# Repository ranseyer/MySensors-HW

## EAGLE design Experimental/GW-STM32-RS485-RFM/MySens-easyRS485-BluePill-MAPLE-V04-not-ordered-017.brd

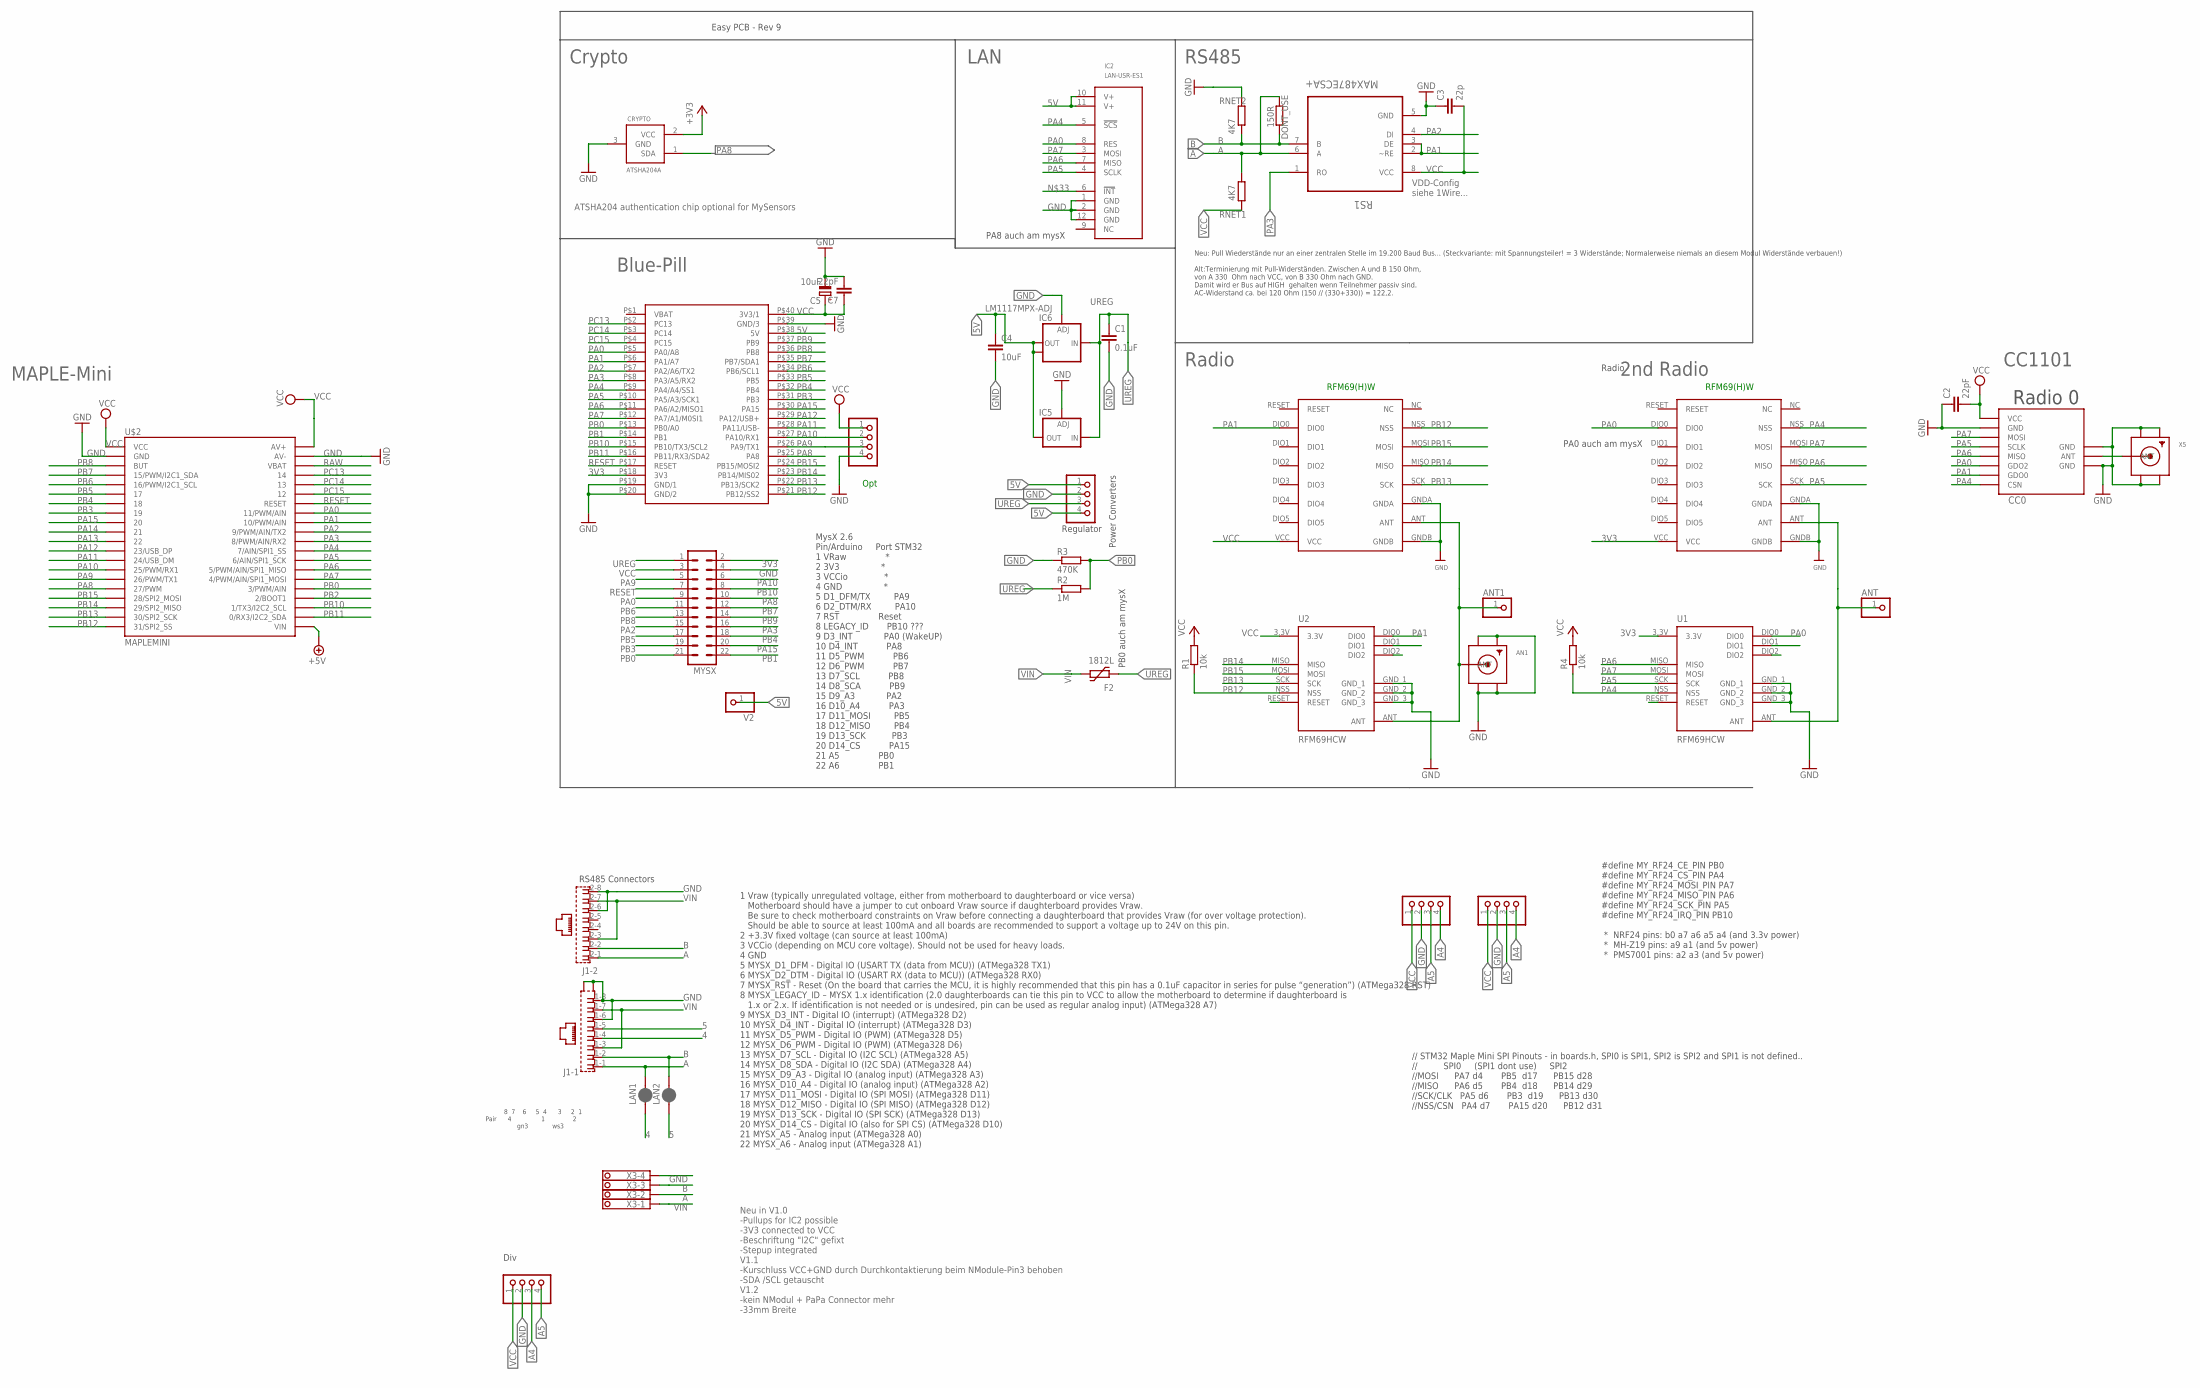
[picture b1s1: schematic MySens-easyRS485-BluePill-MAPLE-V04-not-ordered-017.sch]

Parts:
AN1: SMACONNECTOR_EDGE; SMA_EDGELAUNCH
ANT, ANT1: PINHD-1X1; 1X01
BH1750: PINHD-1X04_2.54-S; 1X04-S
C1: 0.1uF; C1206
C2, C7: 22pF; C0805
C3: 22p; C0805
C4: 10uF; C1210
C5: 10uF; R/2012-12W
CC0: CC1101; CC1101_MODULE1_SMD
CRYPTO: ATSHA204A; SOT23
DBG: PINHD-1X04_2.54-S; 1X04-S
DONT_USE: 150R; R0805
F2: 1812L
I2C-1, I2C-2: PINHD-1X04_2.54-S; 1X04-S
IC2: LAN-USR-ES1; USR-ES1
IC5: LD117ADT50TR; DPACK
IC6: LM1117MPX-ADJ; SOT223
J1: RJ45_2X_NARROW_SHILDPINS_NOCASE
LAN1, LAN2: JUMPER-SMT_2_NC_PASTE_SILK; SMT-JUMPER_2_NC_PASTE_SILK
MYSX: MA11-2
R1, R4: 10k; M0805
R2: 1M; R0805
R3: 470K; R0805
RFM69W, RFM69W1: RFM69HW; RFM
RNET1, RNET2: 4K7; R0805
RS1: MAX487ECSA+; SOIC127P600X175-8N
STEPDWN: PINHD-1X04_2.54-S; 1X04-S
U1, U2: RFM69HCW; RFM69HCW-XXXS2
U$2: MAPLEMINI; 20-DIP
U$4: BLUEPILL
V2: PINHD-1X1; 1X01
X3: 1751264
X5: SMACONNECTOR_EDGE; SMA_EDGELAUNCH

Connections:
3V3: CRYPTO.2 (VCC), MYSX.2, RFM69W.VCC, U1.3.3V, U$4.P$18 (3V3)
4: J1.1-4 (4), LAN1.1
5: J1.1-5 (5), LAN2.1
5V: C4.1, IC2.10 (V+), IC2.11 (V+), IC5.4 (OUT), IC6.2 (OUT), IC6.TAB (OUT1), STEPDWN.1, STEPDWN.4, U$4.P$38 (5V), V2.1
+5V: U$2.21 (VIN)
A: DONT_USE.1, J1.1-1 (1), J1.2-1 (1), LAN1.2, RNET1.2, RS1.6 (A), X3.2
A4: BH1750.4, I2C-1.4, I2C-2.3
A5: BH1750.3, I2C-1.3, I2C-2.4
ANT0: CC0.ANT, X5.P (ANT)
ANT1: AN1.P (ANT), ANT1.1, RFM69W1.ANT, U2.ANT
ANT2: ANT.1, RFM69W.ANT, U1.ANT
B: DONT_USE.2, J1.1-2 (2), J1.2-2 (2), LAN2.2, RNET2.1, RS1.7 (B), X3.3
GND: AN1.GND@1 (GND4), AN1.GND@2 (GND3), AN1.GND@3 (GND2), AN1.GND@4 (GND1), BH1750.2, C1.2, C2.1, C3.1, C4.2, C5.-, C7.2, CC0.GND@0 (GND), CC0.GND@1 (GND), CC0.GND@2 (GND), CRYPTO.3 (GND), DBG.4, I2C-1.2, I2C-2.2, IC2.1 (GND), IC2.2 (GND), IC2.12 (GND), IC5.1 (ADJ), IC6.1 (ADJ), J1.1-6 (6), J1.1-8 (8), J1.2-6 (6), J1.2-8 (8), J1.G1 (S1), J1.G3 (S2), MYSX.4, R3.1, RFM69W.GNDA, RFM69W.GNDB, RFM69W1.GNDA, RFM69W1.GNDB, RNET2.2, RS1.5 (GND), STEPDWN.2, U1.GND_1, U1.GND_2, U1.GND_3, U2.GND_1, U2.GND_2, U2.GND_3, U$2.2 (GND), U$2.39 (AV-), U$4.P$19 (GND/1), U$4.P$20 (GND/2), U$4.P$39 (GND/3), X3.4, X5.GND@1 (GND4), X5.GND@2 (GND3), X5.GND@3 (GND2), X5.GND@4 (GND1)
PA0: CC0.GDO2, IC2.8 (RES), MYSX.9, RFM69W.DIO0, U1.DIO0, U$2.33 (11/PWM/AIN), U$4.P$5 (PA0/A8)
PA1: CC0.GDO0, RFM69W1.DIO0, RS1.2 (~RE), RS1.3 (DE), U2.DIO0, U$2.32 (10/PWM/AIN), U$4.P$6 (PA1/A7)
PA2: MYSX.15, RS1.4 (DI), U$2.31 (9/PWM/AIN/TX2), U$4.P$7 (PA2/A6/TX2)
PA3: MYSX.16, RS1.1 (RO), U$2.30 (8/PWM/AIN/RX2), U$4.P$8 (PA3/A5/RX2)
PA4: CC0.CSN, IC2.5 (!SCS!), R4.1, RFM69W.NSS, U1.NSS, U$2.29 (7/AIN/SPI1_SS), U$4.P$9 (PA4/A4/SS1)
PA5: CC0.SCLK, IC2.4 (SCLK), RFM69W.SCK, U1.SCK, U$2.28 (6/AIN/SPI1_SCK), U$4.P$10 (PA5/A3/SCK1)
PA6: CC0.MISO, IC2.7 (MISO), RFM69W.MISO, U1.MISO, U$2.27 (5/PWM/AIN/SPI1_MISO), U$4.P$11 (PA6/A2/MISO1)
PA7: CC0.MOSI, IC2.3 (MOSI), RFM69W.MOSI, U1.MOSI, U$2.26 (4/PWM/AIN/SPI1_MOSI), U$4.P$12 (PA7/A1/M0SI1)
PA8: CRYPTO.1 (SDA), MYSX.10, U$2.16 (27/PWM), U$4.P$25 (PA8)
PA9: DBG.3, MYSX.5, U$2.15 (26/PWM/TX1), U$4.P$26 (PA9/TX1)
PA10: DBG.2, MYSX.6, U$2.14 (25/PWM/RX1), U$4.P$27 (PA10/RX1)
PA11: U$2.13 (24/USB_DM), U$4.P$28 (PA11/USB-)
PA12: U$2.12 (23/USB_DP), U$4.P$29 (PA12/USB+)
PA13: U$2.11 (22)
PA14: U$2.10 (21)
PA15: MYSX.20, U$2.9 (20), U$4.P$30 (PA15)
PB0: MYSX.21, R2.2, R3.2, U$2.25 (3/PWM/AIN), U$4.P$13 (PB0/A0)
PB1: MYSX.22, U$4.P$14 (PB1)
PB2: U$2.24 (2/BOOT1)
PB3: MYSX.19, U$2.8 (19), U$4.P$31 (PB3)
PB4: MYSX.18, U$2.7 (18), U$4.P$32 (PB4)
PB5: MYSX.17, U$2.6 (17), U$4.P$33 (PB5)
PB6: MYSX.11, U$2.5 (16/PWM/I2C1_SCL), U$4.P$34 (PB6/SCL1)
PB7: MYSX.12, U$2.4 (15/PWM/I2C1_SDA), U$4.P$35 (PB7/SDA1)
PB8: MYSX.13, U$2.3 (BUT), U$4.P$36 (PB8)
PB9: MYSX.14, U$4.P$37 (PB9)
PB10: MYSX.8, U$2.23 (1/TX3/I2C2_SCL), U$4.P$15 (PB10/TX3/SCL2)
PB11: U$2.22 (0/RX3/I2C2_SDA), U$4.P$16 (PB11/RX3/SDA2)
PB12: R1.1, RFM69W1.NSS, U2.NSS, U$2.20 (31/SPI2_SS), U$4.P$21 (PB12/SS2)
PB13: RFM69W1.SCK, U2.SCK, U$2.19 (30/SPI2_SCK), U$4.P$22 (PB13/SCK2)
PB14: RFM69W1.MISO, U2.MISO, U$2.18 (29/SPI2_MISO), U$4.P$23 (PB14/MIS02)
PB15: RFM69W1.MOSI, U2.MOSI, U$2.17 (28/SPI2_MOSI), U$4.P$24 (PB15/MOSI2)
PC13: U$2.37 (14), U$4.P$2 (PC13)
PC14: U$2.36 (13), U$4.P$3 (PC14)
PC15: U$2.35 (12), U$4.P$4 (PC15)
RAW: U$2.38 (VBAT)
RESET: MYSX.7, U$2.34 (RESET), U$4.P$17 (RESET)
UREG: C1.1, F2.P$1 (1), IC5.3 (IN), IC6.3 (IN), MYSX.1, R2.1, STEPDWN.3
VCC: BH1750.1, C2.2, C3.2, C5.+, C7.1, CC0.VCC, DBG.1, I2C-1.1, I2C-2.1, MYSX.3, R1.2, R4.2, RFM69W1.VCC, RNET1.1, RS1.8 (VCC), U2.3.3V, U$2.1 (VCC), U$2.40 (AV+), U$4.P$40 (3V3/1)
VIN: F2.P$2 (2), J1.1-3 (3), J1.1-7 (7), J1.2-3 (3), J1.2-7 (7), X3.1

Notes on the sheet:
Easy PCB - Rev 9
ATSHA204 authentication chip optional for MySensors
RFM69(H)W
Radio
VDD-Config siehe 1Wire...
Neu: Pull Wiederstände nur an einer zentralen Stelle im 19.200 Baud Bus... (Steckvariante: mit Spannungsteiler! = 3 Widerstände; Normalerweise niemals an diesem Modul Widerstände verbauen!) Alt:Terminierung mit Pull-Widerständen. Zwischen A und B 150 Ohm, von A 330 Ohm nach VCC, von B 330 Ohm nach 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
Opt
Blue-Pill
// STM32 Maple Mini SPI Pinouts - in boards.h, SPI0 is SPI1, SPI2 is SPI2 and SPI1 is not defined.. // SPI0 (SPI1 dont use) SPI2 //MOSI PA7 d4 PB5 d17 PB15 d28 //MISO PA6 d5 PB4 d18 PB14 d29 //SCK/CLK PA5 d6 PB3 d19 PB13 d30 //NSS/CSN PA4 d7 PA15 d20 PB12 d31
#define MY_RF24_CE_PIN PB0 #define MY_RF24_CS_PIN PA4 #define MY_RF24_MOSI_PIN PA7 #define MY_RF24_MISO_PIN PA6 #define MY_RF24_SCK_PIN PA5 #define MY_RF24_IRQ_PIN PB10 * NRF24 pins: b0 a7 a6 a5 a4 (and 3.3v power) * MH-Z19 pins: a9 a1 (and 5v power) * PMS7001 pins: a2 a3 (and 5v power)
Power Converters
Regulator
Div
Neu in V1.0 -Pullups for IC2 possible -3V3 connected to VCC -Beschriftung "I2C" gefixt -Stepup integrated V1.1 -Kurschluss VCC+GND durch Durchkontaktierung beim NModule-Pin3 behoben -SDA /SCL getauscht V1.2 -kein NModul + PaPa Connector mehr -33mm Breite
8 7 6 5 4 3 2 1 Pair 4 1 2 gn3 ws3
RS485 Connectors
1 Vraw (typically unregulated voltage, either from motherboard to daughterboard or vice versa) Motherboard should have a jumper to cut onboard Vraw source if daughterboard provides Vraw. Be sure to check motherboard constraints on Vraw before connecting a daughterboard that provides Vraw (for over 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
MysX 2.6 Pin/Arduino Port STM32 1 VRaw * 2 3V3 * 3 VCCio * 4 GND * 5 D1_DFM/TX PA9 6 D2_DTM/RX PA10 7 RST Reset 8 LEGACY_ID PB10 ??? 9 D3_INT PA0 (WakeUP) 10 D4_INT PA8 11 D5_PWM PB6 12 D6_PWM PB7 13 D7_SCL PB8 14 D8_SCA PB9 15 D9_A3 PA2 16 D10_A4 PA3 17 D11_MOSI PB5 18 D12_MISO PB4 19 D13_SCK PB3 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
PA0 auch am mysX
PB0 auch am mysX
PA8 auch am mysX
2nd Radio
LAN
RS485
Crypto
Radio 0
CC1101
MAPLE-Mini

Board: 2 copper layers, 41 parts (18 on the bottom side), 48 nets, no tracks yet.

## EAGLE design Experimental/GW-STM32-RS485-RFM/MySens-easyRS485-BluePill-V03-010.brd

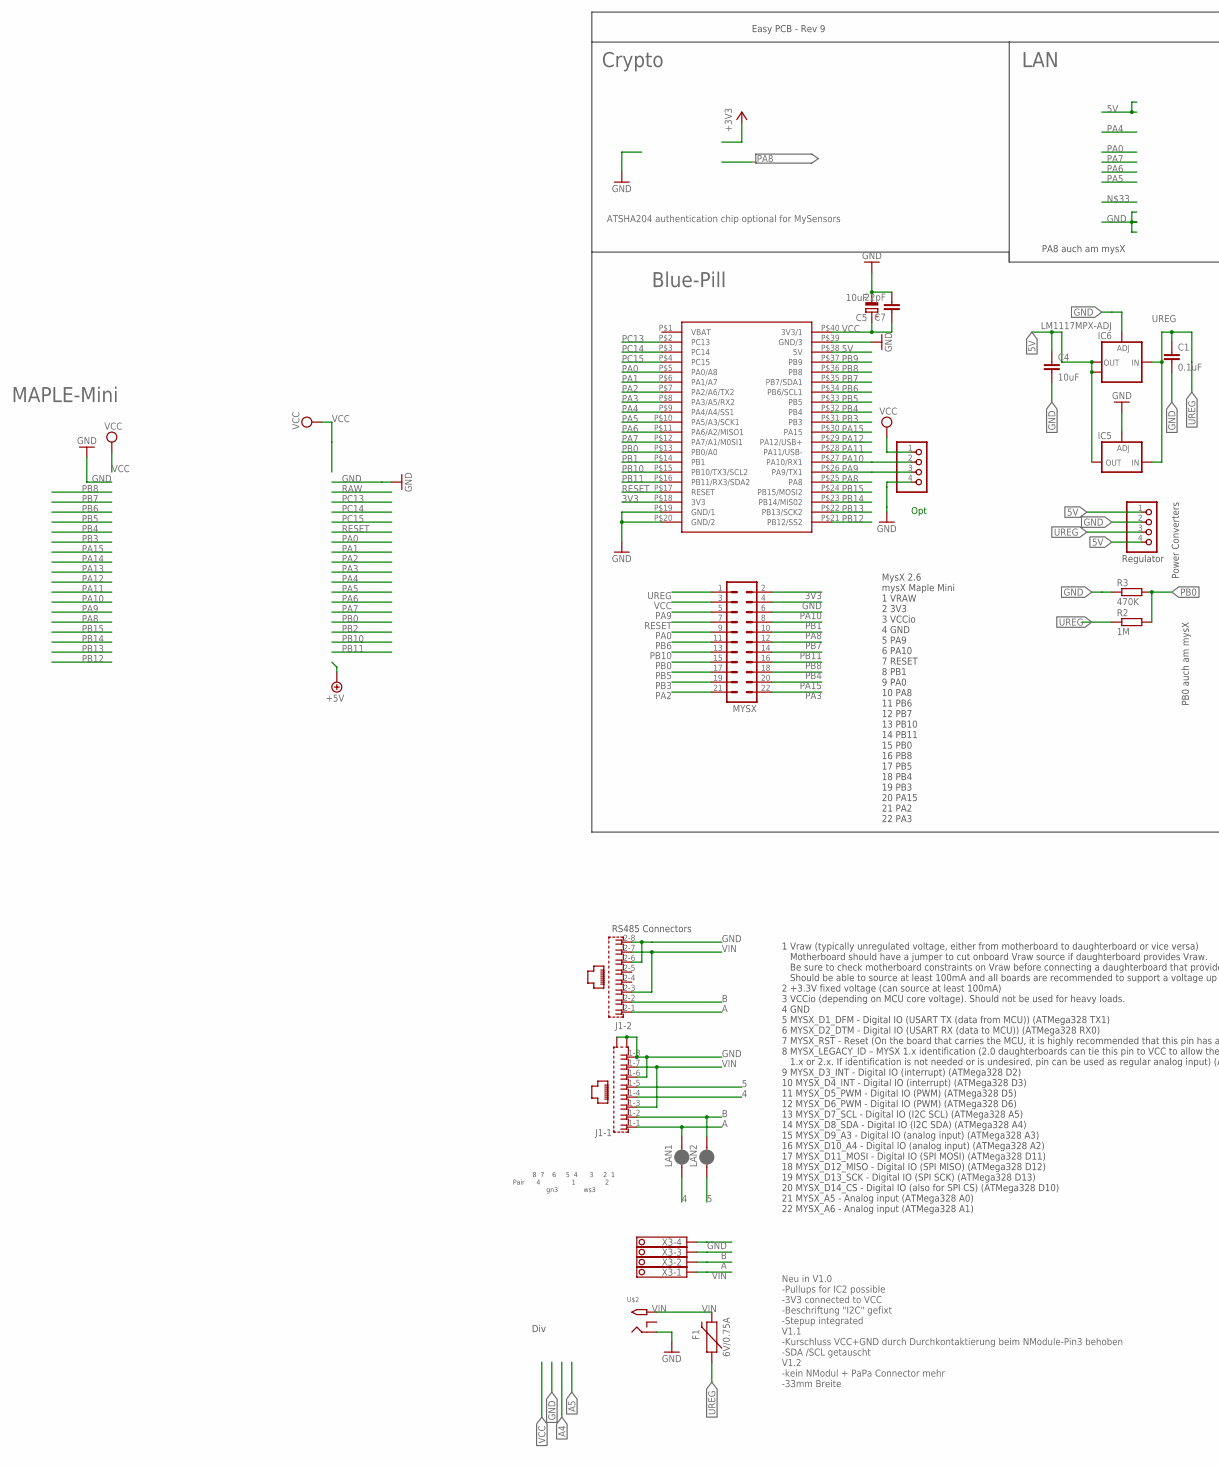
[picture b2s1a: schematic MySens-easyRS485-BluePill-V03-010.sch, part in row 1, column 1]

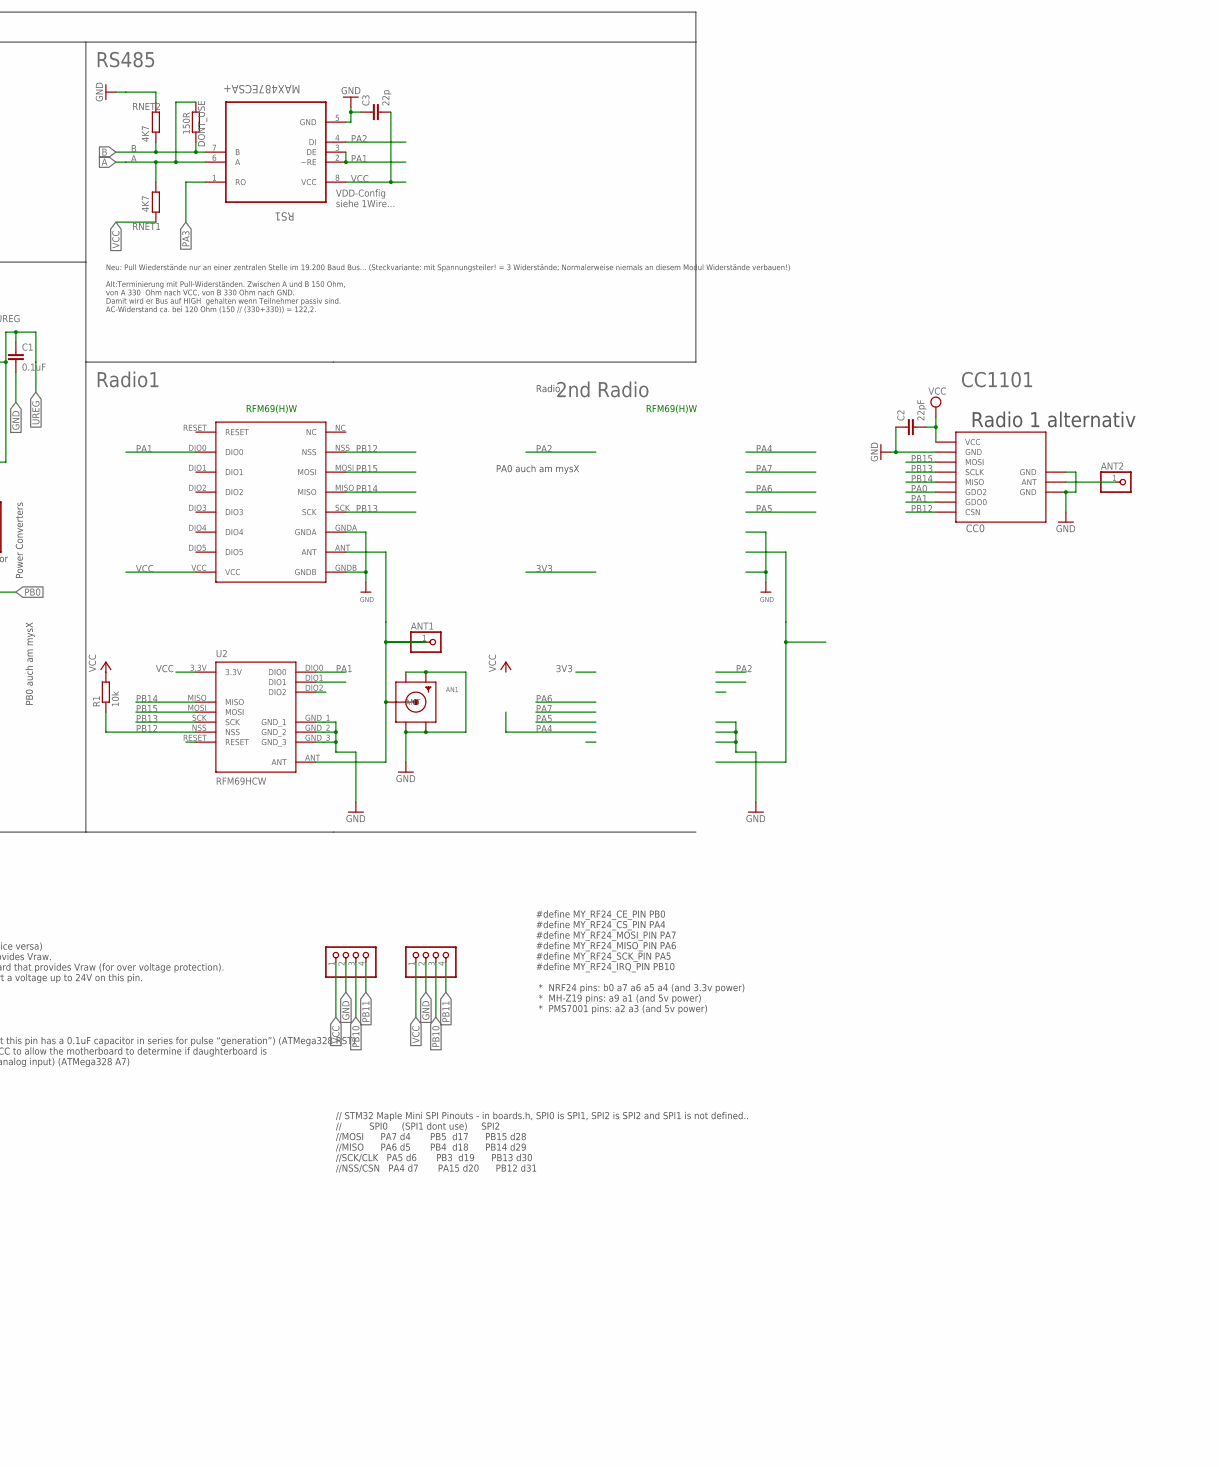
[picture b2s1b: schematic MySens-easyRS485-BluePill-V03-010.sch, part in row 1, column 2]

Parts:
AN1: SMACONNECTOR_EDGE; SMA_EDGELAUNCH
ANT1, ANT2: PINHD-1X1; 1X01
BH1750: PINHD-1X04_2.54-S; 1X04-S
C1: 0.1uF; C1206
C2, C7: 22pF; C0805
C3: 22p; C0805
C4: 10uF; C1210
C5: 10uF; R/2012-12W
CC0: CC1101; CC1101_MODULE1_SMD
DBG: PINHD-1X04_2.54-S; 1X04-S
DONT_USE: 150R; R0805
F1: 6V/0.75A; 1206
I2C-1: PINHD-1X04_2.54-S; 1X04-S
IC5: LD117ADT50TR; DPACK
IC6: LM1117MPX-ADJ; SOT223
J1: RJ45_2X_S
LAN1, LAN2: JUMPER-SMT_2_NC_PASTE_SILK; SMT-JUMPER_2_NC_PASTE_SILK
MYSX: MA11-2
R1: 10k; M0805
R2: 1M; R0805
R3: 470K; R0805
RFM69W1: RFM69HW; RFM
RNET1, RNET2: 4K7; R0805
RS1: MAX487ECSA+; SOIC127P600X175-8N
STEPDWN: PINHD-1X04_2.54-S; 1X04-S
U2: RFM69HCW; RFM69HCW-XXXS2
U$2: 2.1MMJACKTHM; PJ-102A
U$4: BLUEPILL
X3: 1751264

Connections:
3V3: MYSX.2, U$4.P$18 (3V3)
4: J1.1-4 (4), LAN1.1
5: J1.1-5 (5), LAN2.1
5V: C4.1, IC5.4 (OUT), IC6.2 (OUT), IC6.TAB (OUT1), STEPDWN.1, STEPDWN.4, U$4.P$38 (5V)
A: DONT_USE.1, J1.1-1 (1), J1.2-1 (1), LAN1.2, RNET1.2, RS1.6 (A), X3.2
ANT0: ANT2.1, CC0.ANT
ANT1: AN1.P (ANT), ANT1.1, RFM69W1.ANT, U2.ANT
B: DONT_USE.2, J1.1-2 (2), J1.2-2 (2), LAN2.2, RNET2.1, RS1.7 (B), X3.3
GND: AN1.GND@1 (GND4), AN1.GND@2 (GND3), AN1.GND@3 (GND2), AN1.GND@4 (GND1), BH1750.2, C1.2, C2.1, C3.1, C4.2, C5.-, C7.2, CC0.GND@0 (GND), CC0.GND@1 (GND), CC0.GND@2 (GND), DBG.4, I2C-1.2, IC5.1 (ADJ), IC6.1 (ADJ), J1.1-6 (6), J1.1-8 (8), J1.2-6 (6), J1.2-8 (8), J1.G1 (S2), J1.G3 (S1), MYSX.4, R3.1, RFM69W1.GNDA, RFM69W1.GNDB, RNET2.2, RS1.5 (GND), STEPDWN.2, U2.GND_1, U2.GND_2, U2.GND_3, U$2.RING, U$4.P$19 (GND/1), U$4.P$20 (GND/2), U$4.P$39 (GND/3), X3.4
PA0: CC0.GDO2, MYSX.9, U$4.P$5 (PA0/A8)
PA1: CC0.GDO0, RFM69W1.DIO0, RS1.2 (~RE), RS1.3 (DE), U2.DIO0, U$4.P$6 (PA1/A7)
PA2: MYSX.21, RS1.4 (DI), U$4.P$7 (PA2/A6/TX2)
PA3: MYSX.22, RS1.1 (RO), U$4.P$8 (PA3/A5/RX2)
PA4: U$4.P$9 (PA4/A4/SS1)
PA5: U$4.P$10 (PA5/A3/SCK1)
PA6: U$4.P$11 (PA6/A2/MISO1)
PA7: U$4.P$12 (PA7/A1/M0SI1)
PA8: MYSX.10, U$4.P$25 (PA8)
PA9: DBG.3, MYSX.5, U$4.P$26 (PA9/TX1)
PA10: DBG.2, MYSX.6, U$4.P$27 (PA10/RX1)
PA11: U$4.P$28 (PA11/USB-)
PA12: U$4.P$29 (PA12/USB+)
PA15: MYSX.20, U$4.P$30 (PA15)
PB0: MYSX.15, R2.2, R3.2, U$4.P$13 (PB0/A0)
PB1: MYSX.8, U$4.P$14 (PB1)
PB3: MYSX.19, U$4.P$31 (PB3)
PB4: MYSX.18, U$4.P$32 (PB4)
PB5: MYSX.17, U$4.P$33 (PB5)
PB6: MYSX.11, U$4.P$34 (PB6/SCL1)
PB7: MYSX.12, U$4.P$35 (PB7/SDA1)
PB8: MYSX.16, U$4.P$36 (PB8)
PB9: U$4.P$37 (PB9)
PB10: BH1750.3, I2C-1.3, MYSX.13, U$4.P$15 (PB10/TX3/SCL2)
PB11: BH1750.4, I2C-1.4, MYSX.14, U$4.P$16 (PB11/RX3/SDA2)
PB12: CC0.CSN, R1.1, RFM69W1.NSS, U2.NSS, U$4.P$21 (PB12/SS2)
PB13: CC0.SCLK, RFM69W1.SCK, U2.SCK, U$4.P$22 (PB13/SCK2)
PB14: CC0.MISO, RFM69W1.MISO, U2.MISO, U$4.P$23 (PB14/MIS02)
PB15: CC0.MOSI, RFM69W1.MOSI, U2.MOSI, U$4.P$24 (PB15/MOSI2)
PC13: U$4.P$2 (PC13)
PC14: U$4.P$3 (PC14)
PC15: U$4.P$4 (PC15)
RESET: MYSX.7, U$4.P$17 (RESET)
UREG: C1.1, F1.1, IC5.3 (IN), IC6.3 (IN), MYSX.1, R2.1, STEPDWN.3
VCC: BH1750.1, C2.2, C3.2, C5.+, C7.1, CC0.VCC, DBG.1, I2C-1.1, MYSX.3, R1.2, RFM69W1.VCC, RNET1.1, RS1.8 (VCC), U2.3.3V, U$4.P$40 (3V3/1)
VIN: F1.2, J1.1-3 (3), J1.1-7 (7), J1.2-3 (3), J1.2-7 (7), U$2.TIP, X3.1

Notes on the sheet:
Easy PCB - Rev 9
ATSHA204 authentication chip optional for MySensors
RFM69(H)W
Radio
VDD-Config siehe 1Wire...
Neu: Pull Wiederstände nur an einer zentralen Stelle im 19.200 Baud Bus... (Steckvariante: mit Spannungsteiler! = 3 Widerstände; Normalerweise niemals an diesem Modul Widerstände verbauen!) Alt:Terminierung mit Pull-Widerständen. Zwischen A und B 150 Ohm, von A 330 Ohm nach VCC, von B 330 Ohm nach 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
Opt
Blue-Pill
// STM32 Maple Mini SPI Pinouts - in boards.h, SPI0 is SPI1, SPI2 is SPI2 and SPI1 is not defined.. // SPI0 (SPI1 dont use) SPI2 //MOSI PA7 d4 PB5 d17 PB15 d28 //MISO PA6 d5 PB4 d18 PB14 d29 //SCK/CLK PA5 d6 PB3 d19 PB13 d30 //NSS/CSN PA4 d7 PA15 d20 PB12 d31
#define MY_RF24_CE_PIN PB0 #define MY_RF24_CS_PIN PA4 #define MY_RF24_MOSI_PIN PA7 #define MY_RF24_MISO_PIN PA6 #define MY_RF24_SCK_PIN PA5 #define MY_RF24_IRQ_PIN PB10 * NRF24 pins: b0 a7 a6 a5 a4 (and 3.3v power) * MH-Z19 pins: a9 a1 (and 5v power) * PMS7001 pins: a2 a3 (and 5v power)
Power Converters
Regulator
Div
Neu in V1.0 -Pullups for IC2 possible -3V3 connected to VCC -Beschriftung "I2C" gefixt -Stepup integrated V1.1 -Kurschluss VCC+GND durch Durchkontaktierung beim NModule-Pin3 behoben -SDA /SCL getauscht V1.2 -kein NModul + PaPa Connector mehr -33mm Breite
8 7 6 5 4 3 2 1 Pair 4 1 2 gn3 ws3
RS485 Connectors
1 Vraw (typically unregulated voltage, either from motherboard to daughterboard or vice versa) Motherboard should have a jumper to cut onboard Vraw source if daughterboard provides Vraw. Be sure to check motherboard constraints on Vraw before connecting a daughterboard that provides Vraw (for over 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
MysX 2.6 mysX Maple Mini 1 VRAW 2 3V3 3 VCCio 4 GND 5 PA9 6 PA10 7 RESET 8 PB1 9 PA0 10 PA8 11 PB6 12 PB7 13 PB10 14 PB11 15 PB0 16 PB8 17 PB5 18 PB4 19 PB3 20 PA15 21 PA2 22 PA3
PA0 auch am mysX
PB0 auch am mysX
PA8 auch am mysX
Radio1
2nd Radio
LAN
RS485
Crypto
Radio 1 alternativ
CC1101
MAPLE-Mini

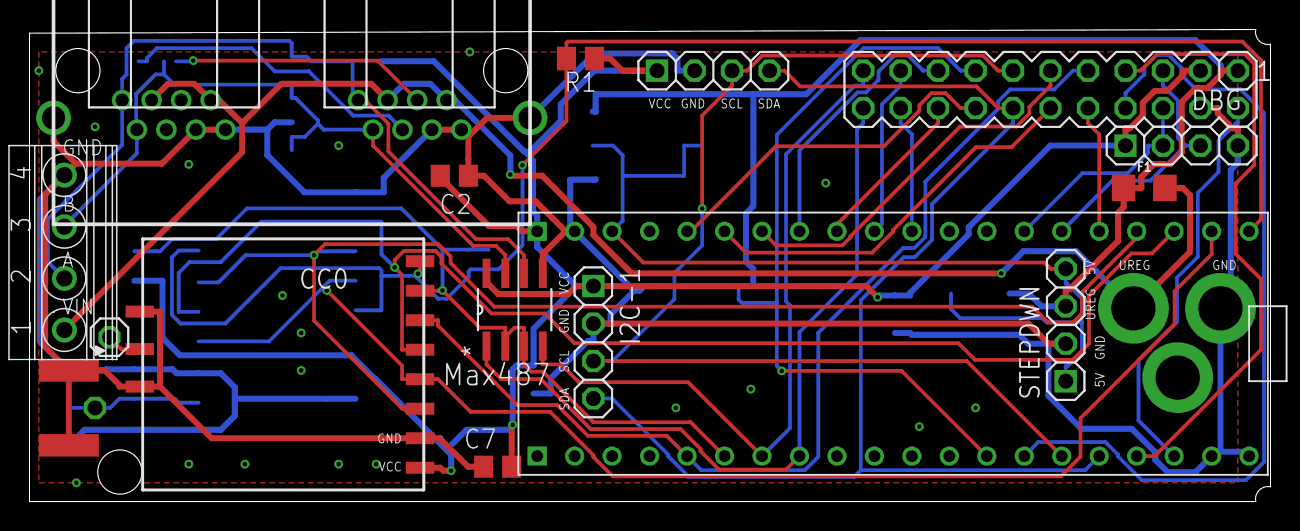
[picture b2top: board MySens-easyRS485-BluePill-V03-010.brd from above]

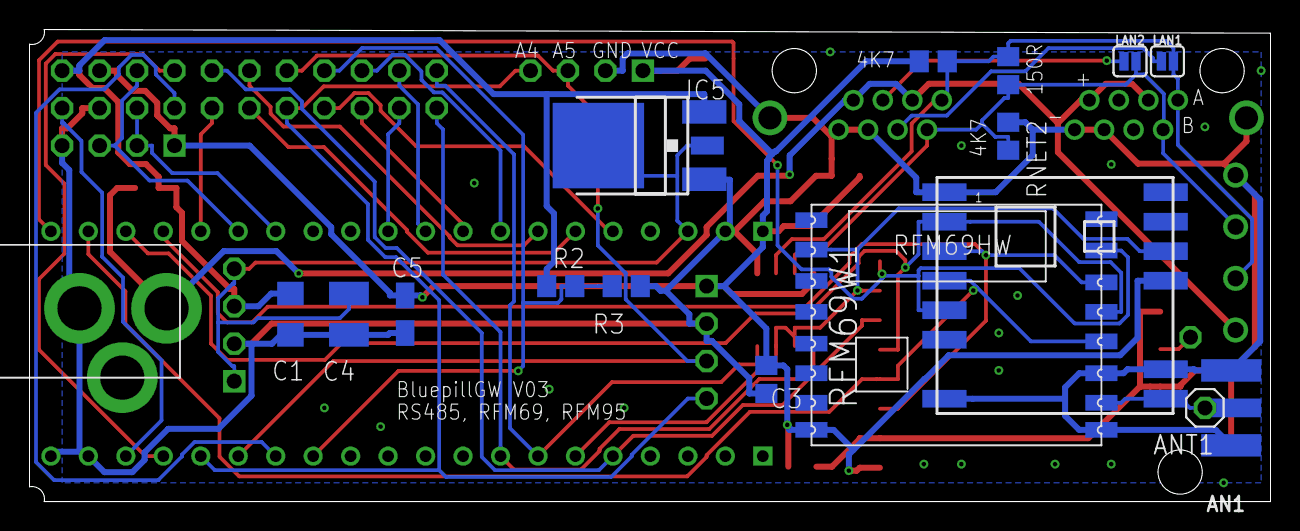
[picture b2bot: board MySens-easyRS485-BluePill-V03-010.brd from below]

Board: 2 copper layers, 84.1 x 32.0 mm, 33 parts (18 on the bottom side), 35 nets.

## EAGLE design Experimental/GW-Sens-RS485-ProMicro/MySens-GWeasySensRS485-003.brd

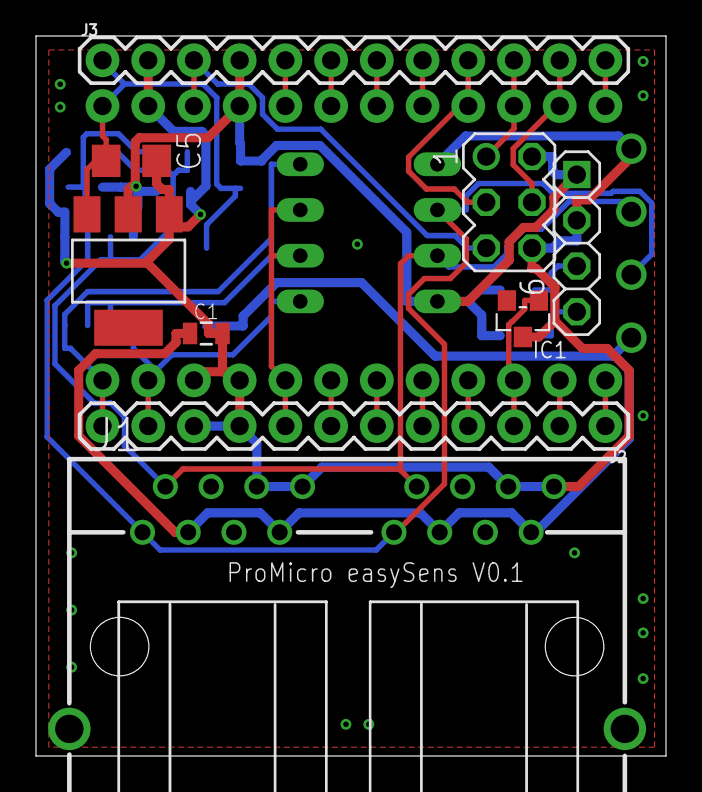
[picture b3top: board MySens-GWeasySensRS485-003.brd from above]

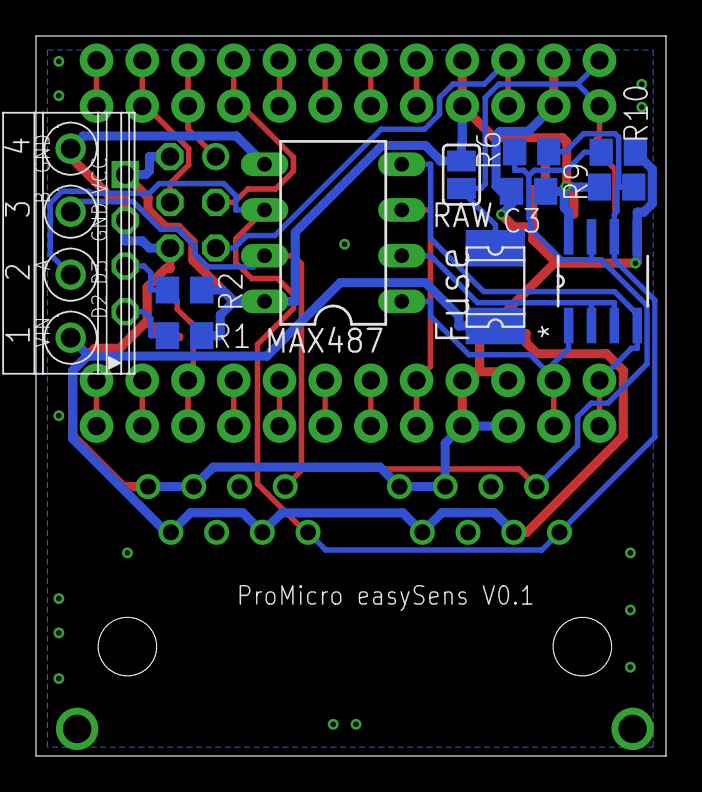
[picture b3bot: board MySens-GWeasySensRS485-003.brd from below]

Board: 2 copper layers, 35.0 x 40.0 mm, 21 parts (11 on the bottom side), 27 nets.

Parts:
1117: REG1117; SOT223
B1: SPARKFUN_PRO_MICRO
C1: 10uF; 0805
C3: 22p; C0805
C5: 0.1uF; C1206
F1: 1812L
IC1: ATSHA204A; SOT23
J1: 557570-1
J2, J3: 1X12
JP10: 1X04-S
MAX487: MAX481CPA; DIL08
R1, R2: 10K; R0805
R6: 150R; R0805
R9, R10: 330R; R0805
RAW: SJ
RS1: MAX487ECSA+; SOIC127P600X175-8N
SV1: MA03-2
X7: 1751264

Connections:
3: B1.6, J2.7
4: B1.7, J2.6
5: B1.8, J2.5
6: B1.9, J2.4
7: B1.10, IC1.1, J2.3
8: B1.11, J2.2
9: B1.12, J2.1
10: B1.13, J3.12
A: J1.1-1, J1.2-1, MAX487.6, R6.1, R9.2, RS1.6, X7.2
A0: B1.17, J3.8
A1: B1.18, J3.7
A2: B1.19, J3.6
A3: B1.20, J3.5
B: J1.1-2, J1.2-2, MAX487.7, R6.2, R10.1, RS1.7, X7.3
D2: JP10.4, R1.2
D3: JP10.3, R2.2
GND: 1117.1, B1.3, B1.4, B1.23, C1.2, C3.1, C5.2, IC1.3, J1.1-6, J1.1-8, J1.2-6, J1.2-8, J2.9, J2.10, J3.2, JP10.2, MAX487.5, R10.2, RS1.5, SV1.6, X7.4
IN: C1.1, F1.P$1, J1.1-3, J1.1-7, J1.2-3, J1.2-7, X7.1
IRQ: B1.5, J2.8, MAX487.2, MAX487.3, RS1.2, RS1.3
MISO: B1.15, J3.10, SV1.1
MOSI: B1.14, J3.11, SV1.4
RAW: 1117.3, B1.24, C5.1, F1.P$2, J3.1, RAW.2
RST: B1.22, J3.3, SV1.5
RX: B1.2, J2.11, MAX487.1, RS1.1
SCK: B1.16, J3.9, SV1.3
TX: B1.1, J2.12, MAX487.4, RS1.4
VCC: 1117.2, B1.21, C3.2, J3.4, JP10.1, MAX487.8, R1.1, R2.1, R9.1, RAW.1, RS1.8, SV1.2

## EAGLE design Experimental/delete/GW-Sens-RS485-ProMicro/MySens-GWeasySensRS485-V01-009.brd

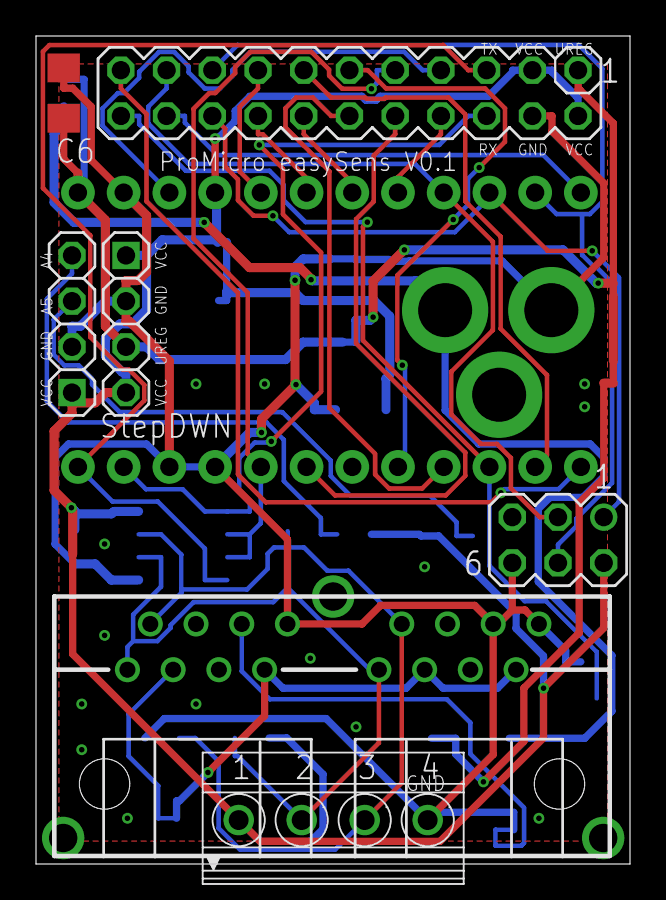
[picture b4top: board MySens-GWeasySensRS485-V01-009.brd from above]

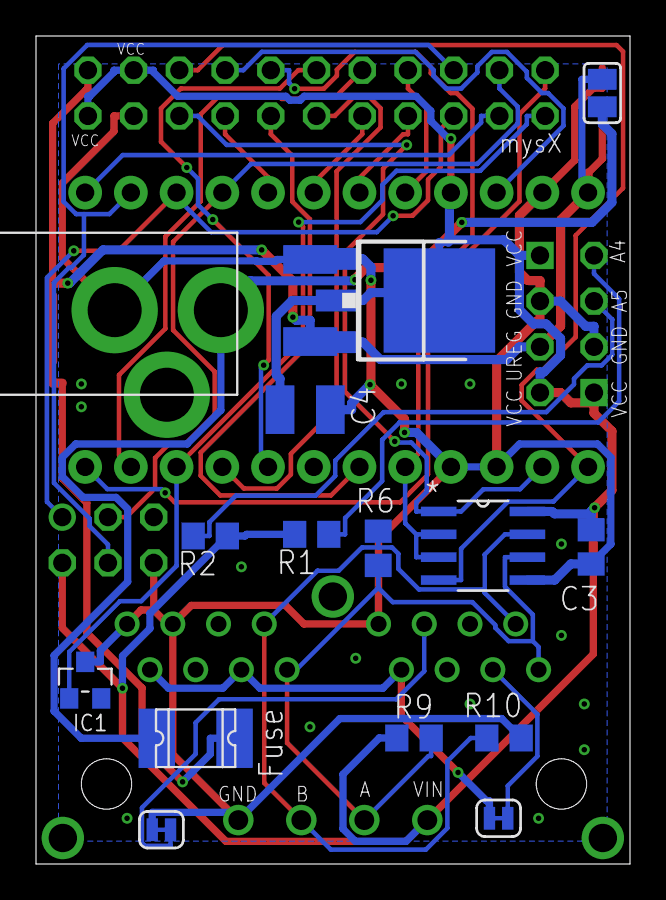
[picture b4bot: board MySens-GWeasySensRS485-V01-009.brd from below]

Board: 2 copper layers, 33.0 x 46.0 mm, 24 parts (16 on the bottom side), 29 nets.

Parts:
B1: SPARKFUN_PRO_MICRO
C3: 22p; C0805
C4: 10uF; C1210
C6: 0.1uF; C1206
F2: 1812L
IC1: ATSHA204A; SOT23
IC2: LD117ADT50TR; DPACK
IC6: LM1117MPX-ADJ; SOT223
J4: RJ45_2X_NARROW_SHILDPINS_NOCASE
JP1, JP3: JUMPER-SMT_2_NC_TRACE_SILK; SMT-JUMPER_2_NC_TRACE_SILK
JP10: 1X04-S
R1, R2: 10K; R0805
R6: 150R; R0805
R9, R10: 330R; R0805
RAW1: SJ
RS1: MAX487ECSA+; SOIC127P600X175-8N
STEPDWN: 1X04-S
SV1: MA03-2
SV2: MA11-2
U$3: 2.1MMJACKTHM; PJ-102A
X4: 1751264

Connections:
1: J4.1-3, JP1.1
2: J4.1-6, JP3.1
A: J4.1-1, J4.2-1, R6.1, R9.2, RS1.6, X4.2
A0: B1.17, SV2.8
A1: B1.18, SV2.14
A2: B1.19, SV2.16
A3: B1.20, SV2.15
A4: JP10.4, R1.2
A5: JP10.3, R2.2
B: J4.1-2, J4.2-2, R6.2, R10.1, RS1.7, X4.3
D2: B1.5, RS1.2, RS1.3, SV2.9
D3: B1.6, SV2.10
D5: B1.8, SV2.11
D6: B1.9, SV2.12
D7: B1.10, IC1.1, SV2.22
D8: B1.11, SV2.13
D9: B1.12, SV2.21
D10_SS: B1.13, SV2.20
D11_MOSI: B1.14, SV1.4, SV2.17
D12_MISO: B1.15, SV1.1, SV2.18
D13_SCK: B1.16, SV1.3, SV2.19
GND: B1.3, B1.4, B1.23, C3.1, C4.2, C6.2, IC1.3, IC2.1, IC6.1, J4.1-8, J4.2-6, J4.2-8, JP3.2, JP10.2, R10.2, RS1.5, STEPDWN.2, SV1.6, SV2.4, U$3.RING, X4.4
IN: J4.1-7, J4.2-3, J4.2-7, JP1.2
RESET: B1.22, SV2.7
RX0: B1.2, RS1.1, SV2.6
TX1: B1.1, RS1.4, SV2.5
UREG: B1.24, C6.1, F2.P$1, IC2.3, IC6.3, RAW1.2, STEPDWN.3, SV2.1
VCC: B1.21, C3.2, C4.1, IC2.4, IC6.2, IC6.TAB, JP10.1, R1.1, R2.1, R9.1, RS1.8, STEPDWN.1, STEPDWN.4, SV1.2, SV2.2, SV2.3, X4.1
VIN: F2.P$2, RAW1.1, U$3.TIP

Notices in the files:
parts and their libraries:
SparkFun-Jumpers: Licensing: Creative Commons ShareAlike 4.0 International - https://creativecommons.org/licenses/by-sa/4.0
microbuilder: This work is placed in the public domain, and may be freely used for commercial and non-commercial work with the following conditions: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
